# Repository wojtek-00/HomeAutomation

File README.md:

# HomeAutomation

A modular home automation system built around ESPHome, custom PCB design (KiCad), and 3D-printed enclosures.

The project is designed to be **scalable**, allowing multiple independent hardware modules (controller + expanders) that integrate into a single automation system.

---

# 🧠 System Overview

The project is split into two main domains:

## 🧩 hardware/
Contains all physical devices and their design artifacts:

- PCB designs (KiCad)
- 3D enclosures (STEP / CAD files)
- front panels / UI elements
- production-ready snapshots (releases)

Each hardware module is self-contained.

### Current modules:
- `system_controller` – main brain of the system
- `relay_expander` – relay output module (8 outputs + 8 inputs)
- *(future expanders will be added here)*

---

## ⚙️ system/
Contains software and logic:

- ESPHome configurations
- automation logic (e.g. Home Assistant)
- device behavior definitions
- shared system-level configuration

This layer defines **how devices behave**, not how they are built.

---

# 🏗️ Hardware Module Structure

Each hardware module follows the same structure:
 - hardware/<module_name>/
 - current/ # active development (WIP)
 - releases/ # frozen production versions

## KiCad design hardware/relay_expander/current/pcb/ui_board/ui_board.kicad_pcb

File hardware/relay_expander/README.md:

# Sprinkler Expander Module

## Overview

The **Sprinkler Expander Module** is a modular extension board designed for an ESP32-based controller system used with ESPHome home automation projects.

It provides additional digital I/O capabilities as well as flexible power handling for relay-driven actuator systems.

---

## Features

- 8× relay outputs
- 8× digital inputs
- Modular design for sprinkler and automation systems
- Power distribution system with configurable relay supply
- Designed for integration with ESP32 System Controller

---

## Power Architecture

The module contains two independent power domains:

### 1. Logic Power (5V system supply)

- Onboard **bridge rectifier**
- Used to convert optional **AC input into DC**
- Followed by a **5V buck converter**
- Supplies power for:
  - Relay coils
  - ESP32 System Controller (optional power path)

> This allows the system to be powered either from AC or DC sources.

---

### 2. Relay Power Domain

Relay outputs are powered separately from the logic section.

- Default supply: **24VAC (or equivalent external supply)**
- Each relay bank can be powered from a shared rail

#### Individual relay isolation

Each relay channel can be electrically isolated from the main relay power rail by removing a **jumper**.

This allows:
- independent relay supply per channel
- mixed-voltage operation
- custom actuator voltage per output

---

## System Behavior

- Logic section is always powered via 5V rail
- Relay coils may be powered from:
  - shared 24VAC rail (default mode)
  - or independent external supply per channel (jumper removed)

---

## Application

Typical applications:

- Irrigation / sprinkler control systems
- Valve actuation systems
- Distributed relay automation
- Mixed-voltage industrial control logic

---

## Integration

Designed for use with:

- ESP32 System Controller (ESPHome firmware)
- Modular expansion architecture
- DIN rail mounted enclosures

---

## Notes

- Ensure correct jumper configuration before applying relay power
- Do not mix AC and DC relay supply on the same channel
- Verify coil voltage compatibility before deployment

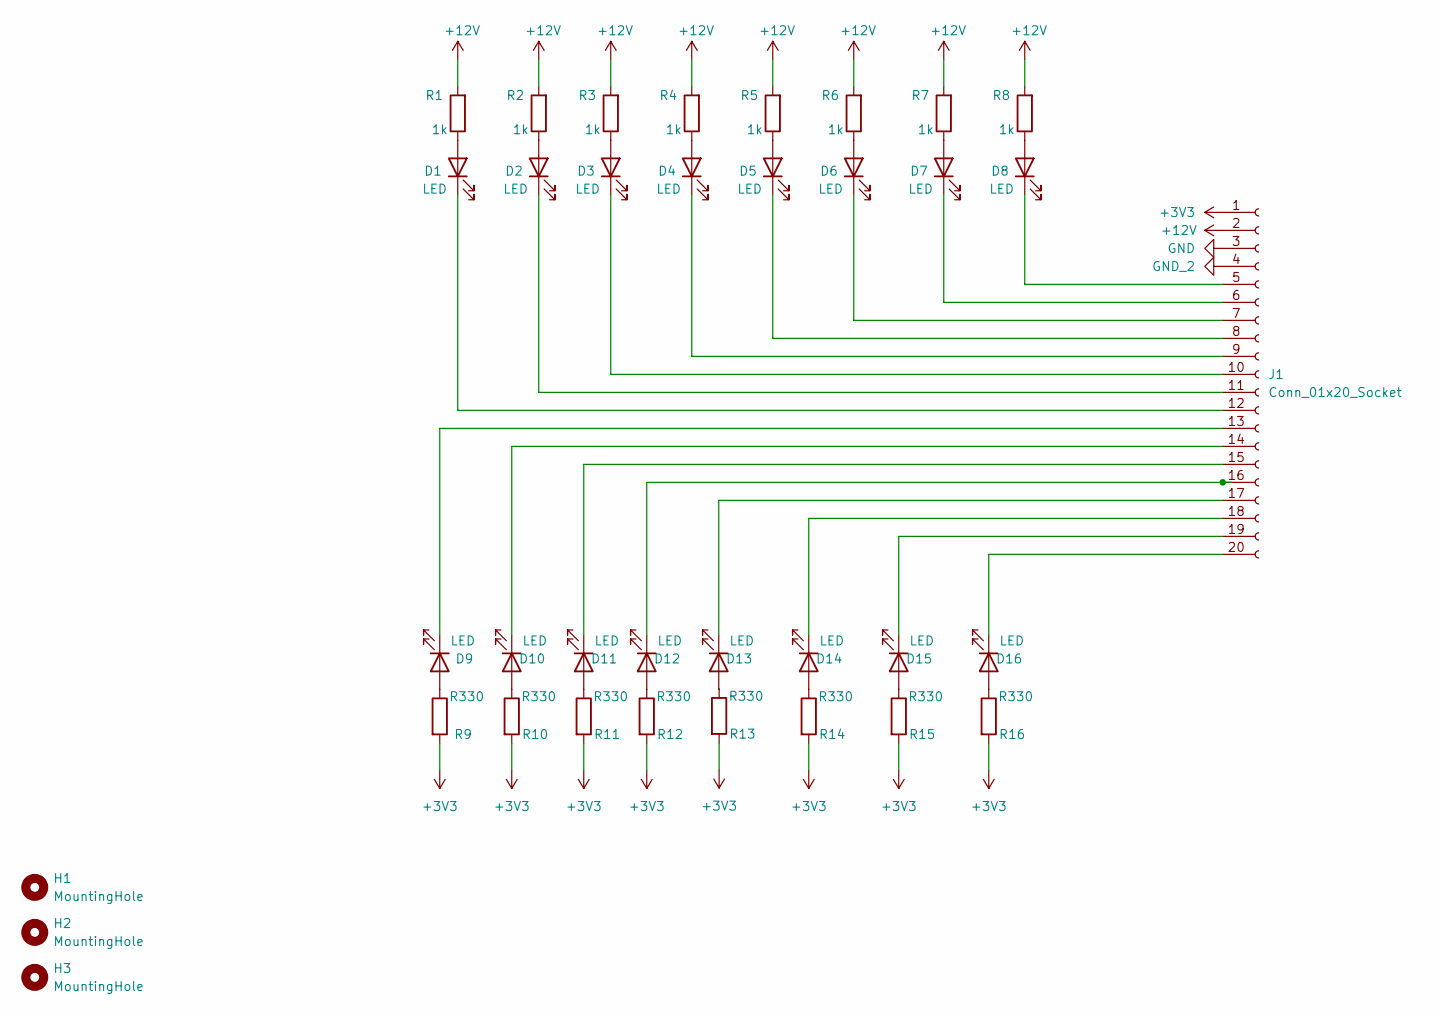
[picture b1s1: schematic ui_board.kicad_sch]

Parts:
D1, D2, D3, D4, D5, D6, D7, D8, D9, D10, D11, D12, D13, D14, D15, D16: LED; LED_1206_3216Metric_Pad1.42x1.75mm_HandSolder
H1, H2, H3: MountingHole; MountingHole_2.2mm_M2_ISO7380_Pad_TopOnly
J1: Conn_01x20_Socket; PinSocket_2x10_P1.27mm_Vertical
R1, R2, R3, R4, R5, R6, R7, R8: 1k; R_1206_3216Metric_Pad1.30x1.75mm_HandSolder
R9, R10, R11, R12, R13, R14, R15, R16: R330; R_1206_3216Metric_Pad1.30x1.75mm_HandSolder

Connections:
+3V3: J1.1, R9.2, R10.2, R11.2, R12.2, R13.2, R14.2, R15.2, R16.2
+12V: J1.2, R1.2, R2.2, R3.2, R4.2, R5.2, R6.2, R7.2, R8.2
GND: J1.3
GND_2: J1.4
unnamed: D1.2 (A), R1.1
unnamed: D1.1 (K), J1.12
unnamed: D2.2 (A), R2.1
unnamed: D2.1 (K), J1.11
unnamed: D3.2 (A), R3.1
unnamed: D3.1 (K), J1.10
unnamed: D4.2 (A), R4.1
unnamed: D4.1 (K), J1.9
unnamed: D5.2 (A), R5.1
unnamed: D5.1 (K), J1.8
unnamed: D6.2 (A), R6.1
unnamed: D6.1 (K), J1.7
unnamed: D7.2 (A), R7.1
unnamed: D7.1 (K), J1.6
unnamed: D8.2 (A), R8.1
unnamed: D8.1 (K), J1.5
unnamed: D9.2 (A), R9.1
unnamed: D9.1 (K), J1.13
unnamed: D10.2 (A), R10.1
unnamed: D10.1 (K), J1.14
unnamed: D11.2 (A), R11.1
unnamed: D11.1 (K), J1.15
unnamed: D12.2 (A), R12.1
unnamed: D12.1 (K), J1.16
unnamed: D13.2 (A), R13.1
unnamed: D13.1 (K), J1.17
unnamed: D14.2 (A), R14.1
unnamed: D14.1 (K), J1.18
unnamed: D15.2 (A), R15.1
unnamed: D15.1 (K), J1.19
unnamed: D16.2 (A), R16.1
unnamed: D16.1 (K), J1.20

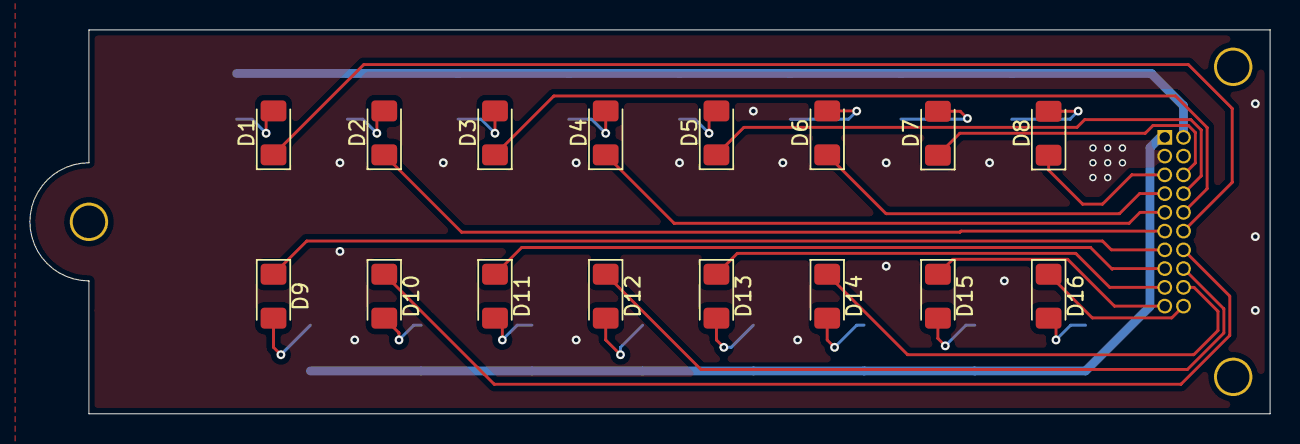
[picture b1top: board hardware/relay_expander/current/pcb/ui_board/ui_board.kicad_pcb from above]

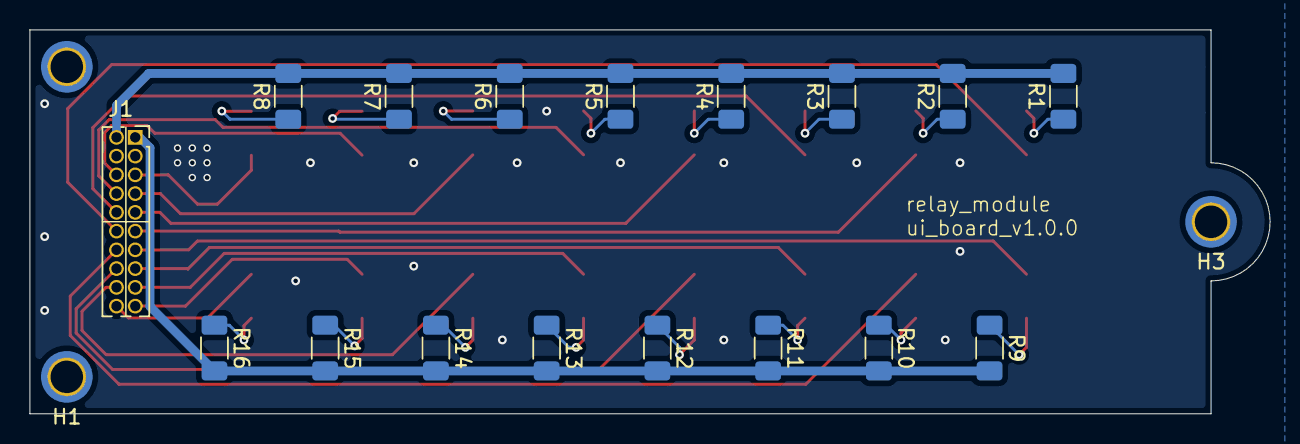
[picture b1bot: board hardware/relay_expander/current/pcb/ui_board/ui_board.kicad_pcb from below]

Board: 2 copper layers, 84.0 x 26.0 mm, 36 parts (20 on the bottom side), 34 nets.

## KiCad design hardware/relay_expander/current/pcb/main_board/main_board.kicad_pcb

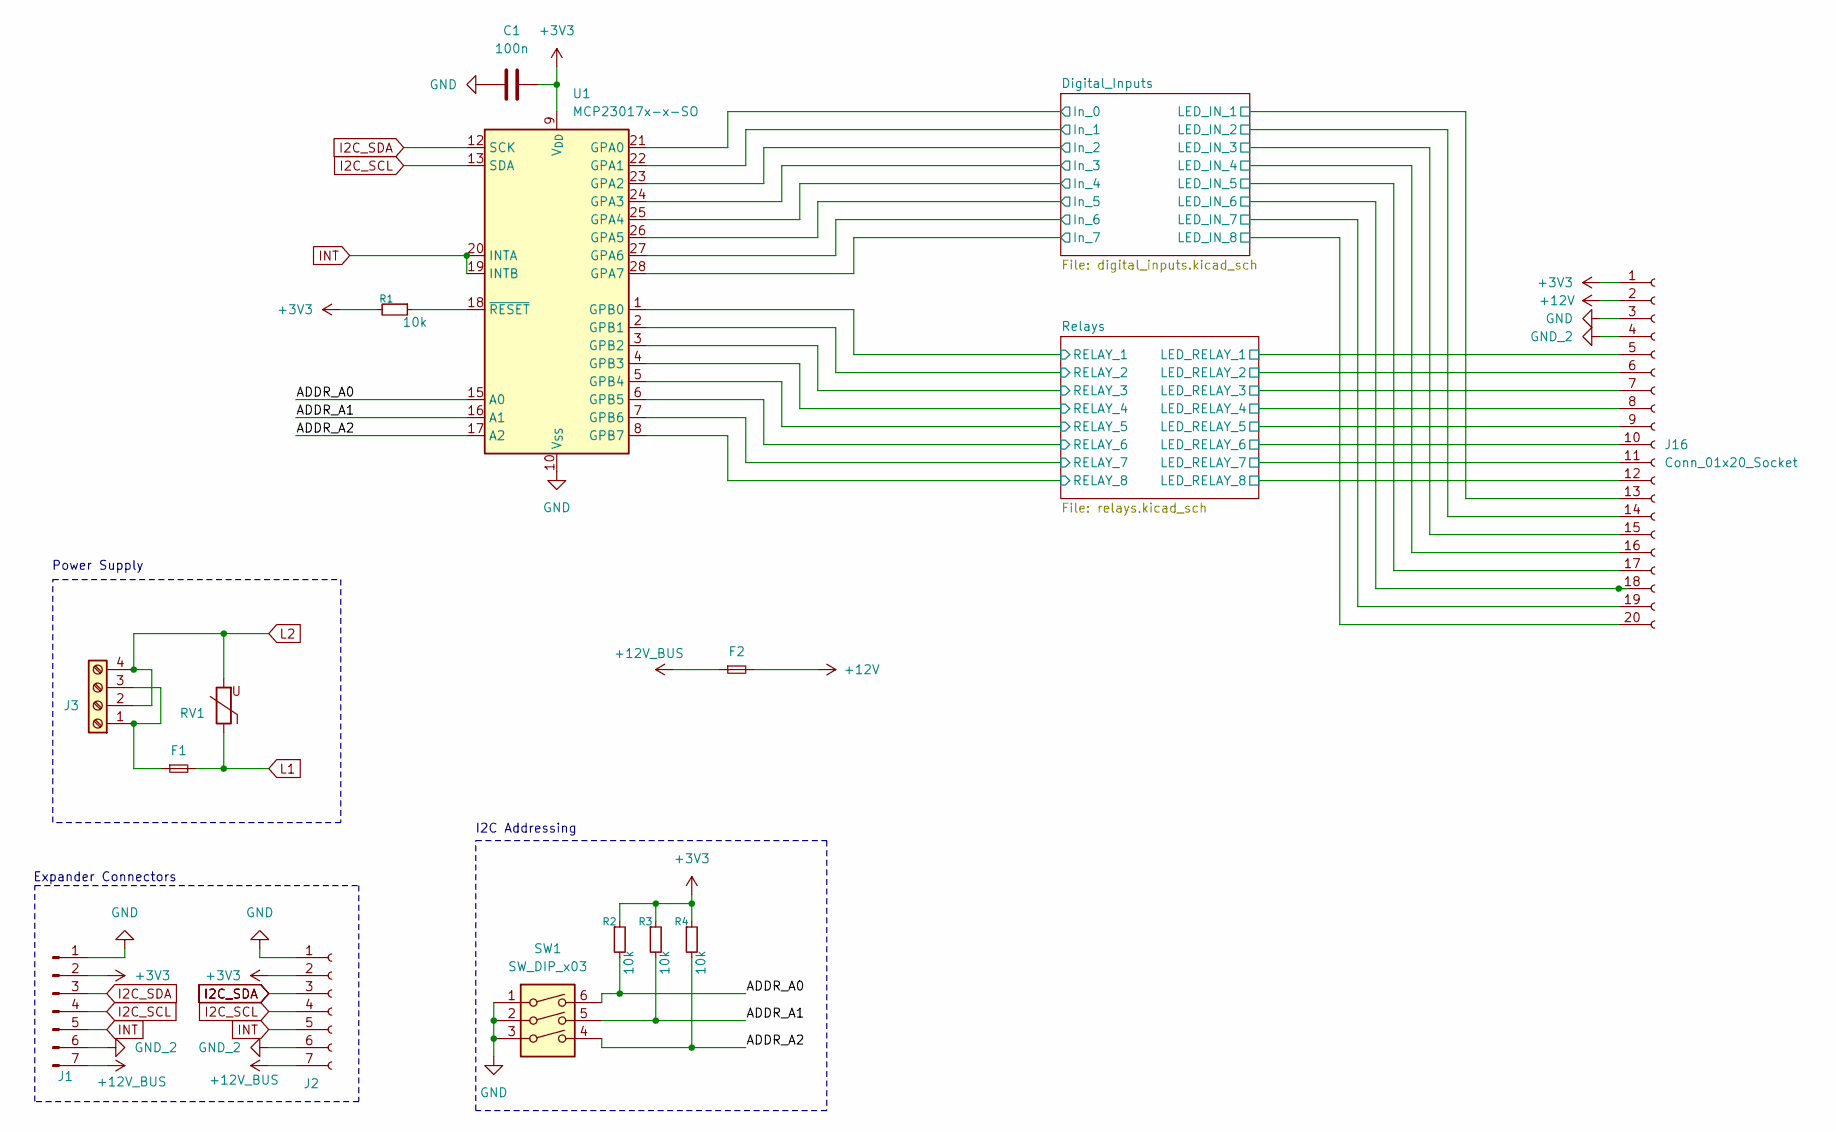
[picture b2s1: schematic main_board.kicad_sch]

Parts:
C1: 100n; C_1206_3216Metric_Pad1.33x1.80mm_HandSolder
F1: 1A, PTC; Fuse_BelFuse_0ZRE0033FF_L11.4mm_W3.8mm
F2: 0.5A; Fuse_1206_3216Metric
J1: Conn_01x07_Socket; PinHeader_1x07_P2.54mm_Horizontal_left
J2: Conn_01x07_Socket; PinSocket_1x07_P2.54mm_Horizontal_Right
J3: Screw_Terminal_01x04; TerminalBlock_Xinya_XY308-2.54-4P_1x04_P2.54mm_Horizontal
J16: Conn_01x20_Socket; PinSocket_2x10_P1.27mm_Vertical
R1, R2, R3, R4: 10k; R_1206_3216Metric_Pad1.30x1.75mm_HandSolder
RV1: 39V, 250A; Fuse_BelFuse_0ZRE0033FF_L11.4mm_W3.8mm
SW1: SW_DIP_x03; SW_DIP_SPSTx03_Slide_6.7x9.18mm_W7.62mm_P2.54mm_LowProfile
U1: MCP23017x-x-SO; SOIC-28W_7.5x17.9mm_P1.27mm

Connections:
+3V3: C1.2, J1.2, J2.2, J16.1, R1.2, R2.1, R3.1, R4.1, U1.9 (V_{DD}); also elsewhere on the board
+12V: F2.2, J16.2; also elsewhere on the board
+12V_BUS: F2.1, J1.7, J2.7
/ADDR_A0: R2.2, SW1.6, U1.15 (A0)
/ADDR_A1: R3.2, SW1.5, U1.16 (A1)
/ADDR_A2: R4.2, SW1.4, U1.17 (A2)
/Digital_Inputs/In_0: J16.13, U1.21 (GPA0); also elsewhere on the board
/Digital_Inputs/In_1: J16.14, U1.22 (GPA1); also elsewhere on the board
/Digital_Inputs/In_2: J16.15, U1.23 (GPA2); also elsewhere on the board
/Digital_Inputs/In_3: J16.16, U1.24 (GPA3); also elsewhere on the board
/Digital_Inputs/In_4: J16.17, U1.25 (GPA4); also elsewhere on the board
/Digital_Inputs/In_5: J16.18, U1.26 (GPA5); also elsewhere on the board
/Digital_Inputs/In_6: J16.19, U1.27 (GPA6); also elsewhere on the board
/Digital_Inputs/In_7: J16.20, U1.28 (GPA7); also elsewhere on the board
/Relays/LED_RELAY_1: J16.5; also elsewhere on the board
/Relays/LED_RELAY_2: J16.6; also elsewhere on the board
/Relays/LED_RELAY_3: J16.7; also elsewhere on the board
/Relays/LED_RELAY_4: J16.8; also elsewhere on the board
/Relays/LED_RELAY_5: J16.9; also elsewhere on the board
/Relays/LED_RELAY_6: J16.10; also elsewhere on the board
/Relays/LED_RELAY_7: J16.11; also elsewhere on the board
/Relays/LED_RELAY_8: J16.12; also elsewhere on the board
/Relays/RELAY_1: U1.1 (GPB0); also elsewhere on the board
/Relays/RELAY_2: U1.2 (GPB1); also elsewhere on the board
/Relays/RELAY_3: U1.3 (GPB2); also elsewhere on the board
/Relays/RELAY_4: U1.4 (GPB3); also elsewhere on the board
/Relays/RELAY_5: U1.5 (GPB4); also elsewhere on the board
/Relays/RELAY_6: U1.6 (GPB5); also elsewhere on the board
/Relays/RELAY_7: U1.7 (GPB6); also elsewhere on the board
/Relays/RELAY_8: U1.8 (GPB7); also elsewhere on the board
GND: C1.1, J1.1, J2.1, J16.3, SW1.1, SW1.2, SW1.3, U1.10 (V_{SS}); also elsewhere on the board
GND_2: J1.6, J2.6, J16.4; also elsewhere on the board
I2C_SCL: J1.4, J2.4, U1.13 (SDA)
I2C_SDA: J1.3, J2.3, U1.12 (SCK)
INT: J1.5, J2.5, U1.19 (INTB), U1.20 (INTA)
L1: F1.2, RV1.1; also elsewhere on the board
L2: J3.2, J3.4, RV1.2; also elsewhere on the board
unnamed: F1.1, J3.1, J3.3
unnamed: R1.1, U1.18 (~RESET)

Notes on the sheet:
Expander Connectors
I2C Addressing
Power Supply

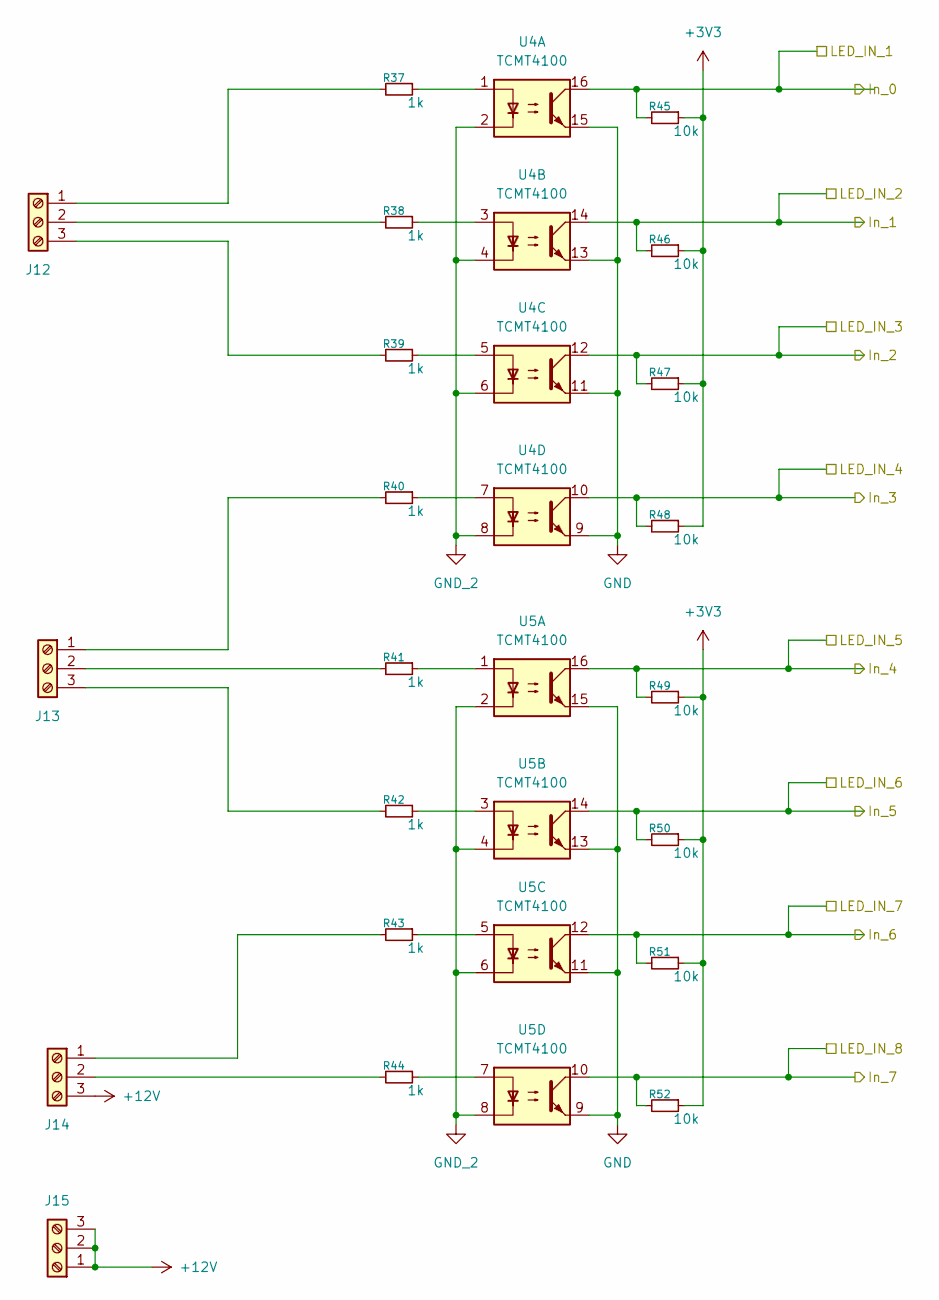
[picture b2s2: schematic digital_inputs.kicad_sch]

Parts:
J12, J13, J14, J15: Screw_Terminal_01x03; TerminalBlock_Phoenix_MPT-0,5-3-2.54_1x03_P2.54mm_Horizontal
R37, R38, R39, R40, R41, R42, R43, R44: 1k; R_1206_3216Metric_Pad1.30x1.75mm_HandSolder
R45, R46, R47, R48, R49, R50, R51, R52: 10k; R_1206_3216Metric_Pad1.30x1.75mm_HandSolder
U4, U5: TCMT4100; SOP-16_4.4x10.4mm_P1.27mm

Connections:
+3V3: R45.1, R46.1, R47.1, R48.1, R49.1, R50.1, R51.1, R52.1; also elsewhere on the board
+12V: J14.3, J15.1, J15.2, J15.3; also elsewhere on the board
/Digital_Inputs/In_0: R45.2, U4.16; also elsewhere on the board
/Digital_Inputs/In_1: R46.2, U4.14; also elsewhere on the board
/Digital_Inputs/In_2: R47.2, U4.12; also elsewhere on the board
/Digital_Inputs/In_3: R48.2, U4.10; also elsewhere on the board
/Digital_Inputs/In_4: R49.2, U5.16; also elsewhere on the board
/Digital_Inputs/In_5: R50.2, U5.14; also elsewhere on the board
/Digital_Inputs/In_6: R51.2, U5.12; also elsewhere on the board
/Digital_Inputs/In_7: R52.2, U5.10; also elsewhere on the board
GND: U4.9, U4.11, U4.13, U4.15, U5.9, U5.11, U5.13, U5.15; also elsewhere on the board
GND_2: U4.2, U4.4, U4.6, U4.8, U5.2, U5.4, U5.6, U5.8; also elsewhere on the board
unnamed: J12.1, R37.2
unnamed: J12.2, R38.2
unnamed: J12.3, R39.2
unnamed: J13.1, R40.2
unnamed: J13.2, R41.2
unnamed: J13.3, R42.2
unnamed: J14.1, R43.2
unnamed: J14.2, R44.2
unnamed: R37.1, U4.1
unnamed: R38.1, U4.3
unnamed: R39.1, U4.5
unnamed: R40.1, U4.7
unnamed: R41.1, U5.1
unnamed: R42.1, U5.3
unnamed: R43.1, U5.5
unnamed: R44.1, U5.7

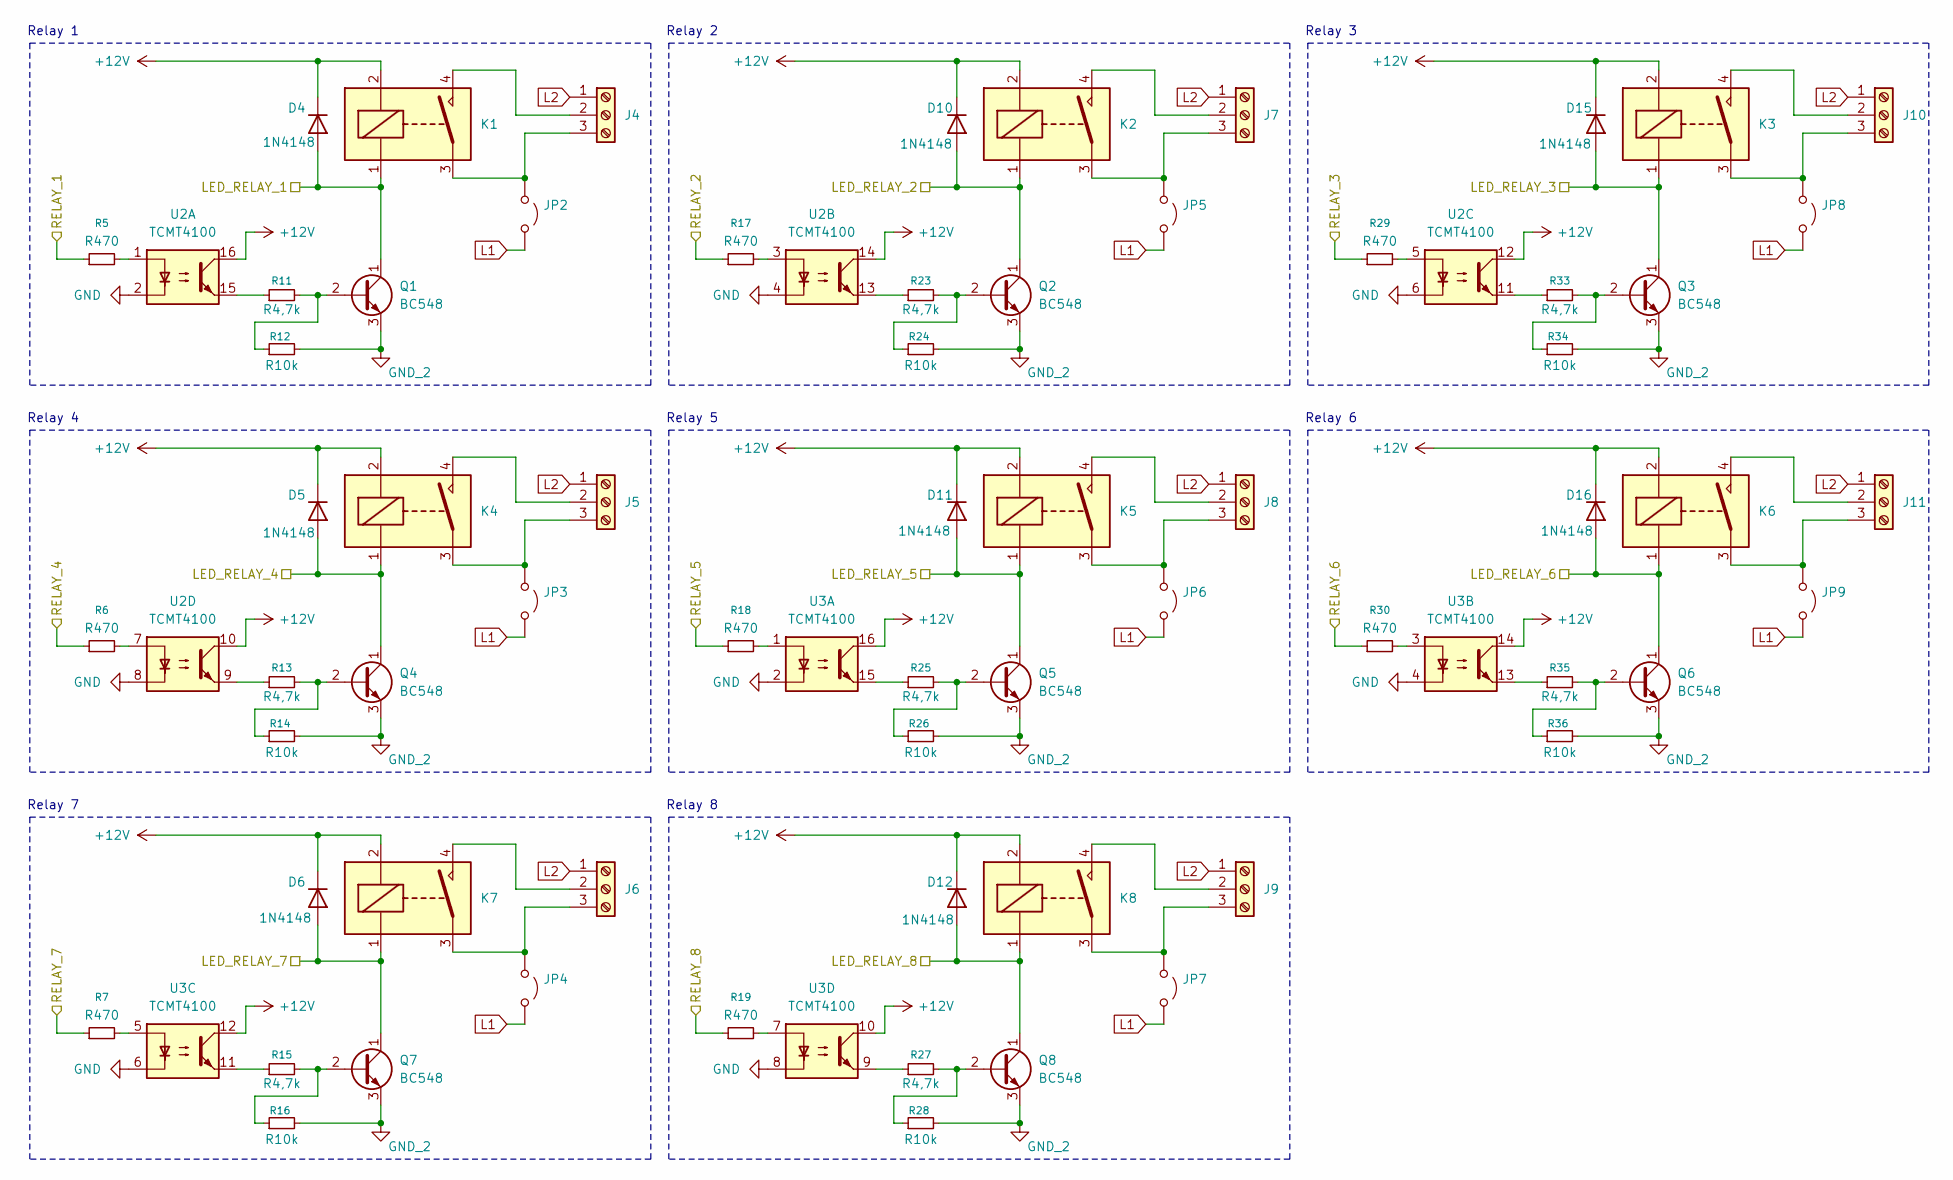
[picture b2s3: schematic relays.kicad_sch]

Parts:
D4, D5, D6, D10, D11, D12, D15, D16: 1N4148; D_SOD-123
J4, J5, J6, J7, J8, J9, J10, J11: Screw_Terminal_01x03; TerminalBlock_Phoenix_MPT-0,5-3-2.54_1x03_P2.54mm_Horizonta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
JP2, JP3, JP4, JP5, JP6, JP7, JP8, JP9: Jumper_2_Open; PinHeader_1x02_P2.54mm_Vertical
K1, K2, K3, K4, K5, K6, K7, K8: HF46F-12-HS1; relay_HF46F
Q1, Q2, Q3, Q4, Q5, Q6, Q7, Q8: BC548; TO-92_Inline
R5, R6, R7, R17, R18, R19, R29, R30: R470; R_1206_3216Metric_Pad1.30x1.75mm_HandSolder
R11, R13, R15, R23, R25, R27, R33, R35: R4,7k; R_1206_3216Metric_Pad1.30x1.75mm_HandSolder
R12, R14, R16, R24, R26, R28, R34, R36: R10k; R_1206_3216Metric_Pad1.30x1.75mm_HandSolder
U2, U3: TCMT4100; SOP-16_4.4x10.4mm_P1.27mm

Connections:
+12V: D4.1 (K), D5.1 (K), D6.1 (K), D10.1 (K), D11.1 (K), D12.1 (K), D15.1 (K), D16.1 (K), K1.2, K2.2, K3.2, K4.2, K5.2, K6.2, K7.2, K8.2, U2.10, U2.12, U2.14, U2.16, U3.10, U3.12, U3.14, U3.16; also elsewhere on the board
/Relays/LED_RELAY_1: D4.2 (A), K1.1, Q1.1 (C); also elsewhere on the board
/Relays/LED_RELAY_2: D10.2 (A), K2.1, Q2.1 (C); also elsewhere on the board
/Relays/LED_RELAY_3: D15.2 (A), K3.1, Q3.1 (C); also elsewhere on the board
/Relays/LED_RELAY_4: D5.2 (A), K4.1, Q4.1 (C); also elsewhere on the board
/Relays/LED_RELAY_5: D11.2 (A), K5.1, Q5.1 (C); also elsewhere on the board
/Relays/LED_RELAY_6: D16.2 (A), K6.1, Q6.1 (C); also elsewhere on the board
/Relays/LED_RELAY_7: D6.2 (A), K7.1, Q7.1 (C); also elsewhere on the board
/Relays/LED_RELAY_8: D12.2 (A), K8.1, Q8.1 (C); also elsewhere on the board
/Relays/RELAY_1: R5.1; also elsewhere on the board
/Relays/RELAY_2: R17.1; also elsewhere on the board
/Relays/RELAY_3: R29.1; also elsewhere on the board
/Relays/RELAY_4: R6.1; also elsewhere on the board
/Relays/RELAY_5: R18.1; also elsewhere on the board
/Relays/RELAY_6: R30.1; also elsewhere on the board
/Relays/RELAY_7: R7.1; also elsewhere on the board
/Relays/RELAY_8: R19.1; also elsewhere on the board
GND: U2.2, U2.4, U2.6, U2.8, U3.2, U3.4, U3.6, U3.8; also elsewhere on the board
GND_2: Q1.3 (E), Q2.3 (E), Q3.3 (E), Q4.3 (E), Q5.3 (E), Q6.3 (E), Q7.3 (E), Q8.3 (E), R12.2, R14.2, R16.2, R24.2, R26.2, R28.2, R34.2, R36.2; also elsewhere on the board
L1: JP2.2 (B), JP3.2 (B), JP4.2 (B), JP5.2 (B), JP6.2 (B), JP7.2 (B), JP8.2 (B), JP9.2 (B); also elsewhere on the board
L2: J4.1, J5.1, J6.1, J7.1, J8.1, J9.1, J10.1, J11.1; also elsewhere on the board
unnamed: J4.2, K1.4
unnamed: J4.3, JP2.1 (A), K1.3
unnamed: J5.2, K4.4
unnamed: J5.3, JP3.1 (A), K4.3
unnamed: J6.2, K7.4
unnamed: J6.3, JP4.1 (A), K7.3
unnamed: J7.2, K2.4
unnamed: J7.3, JP5.1 (A), K2.3
unnamed: J8.2, K5.4
unnamed: J8.3, JP6.1 (A), K5.3
unnamed: J9.2, K8.4
unnamed: J9.3, JP7.1 (A), K8.3
unnamed: J10.2, K3.4
unnamed: J10.3, JP8.1 (A), K3.3
unnamed: J11.2, K6.4
unnamed: J11.3, JP9.1 (A), K6.3
unnamed: Q1.2 (B), R11.2, R12.1
unnamed: Q2.2 (B), R23.2, R24.1
unnamed: Q3.2 (B), R33.2, R34.1
unnamed: Q4.2 (B), R13.2, R14.1
unnamed: Q5.2 (B), R25.2, R26.1
unnamed: Q6.2 (B), R35.2, R36.1
unnamed: Q7.2 (B), R15.2, R16.1
unnamed: Q8.2 (B), R27.2, R28.1
unnamed: R5.2, U2.1
unnamed: R6.2, U2.7
unnamed: R7.2, U3.5
unnamed: R11.1, U2.15
unnamed: R13.1, U2.9
unnamed: R15.1, U3.11
unnamed: R17.2, U2.3
unnamed: R18.2, U3.1
unnamed: R19.2, U3.7
unnamed: R23.1, U2.13
unnamed: R25.1, U3.15
unnamed: R27.1, U3.9
unnamed: R29.2, U2.5
unnamed: R30.2, U3.3
unnamed: R33.1, U2.11
unnamed: R35.1, U3.13

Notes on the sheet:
Relay 3
Relay 8
Relay 2
Relay 7
Relay 6
Relay 5
Relay 4
Relay 1

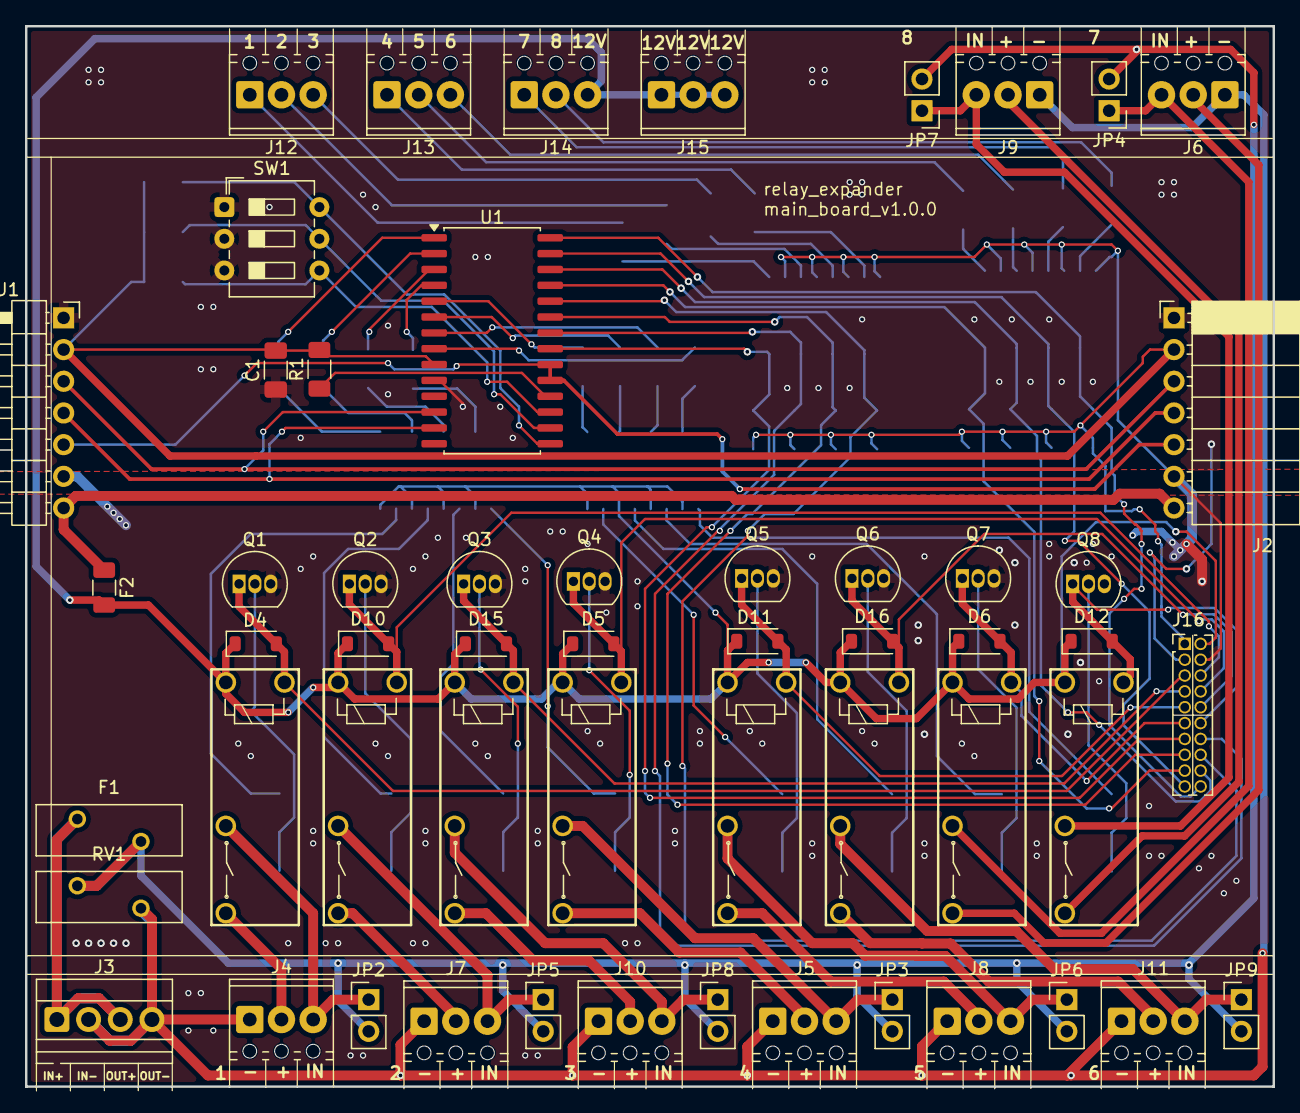
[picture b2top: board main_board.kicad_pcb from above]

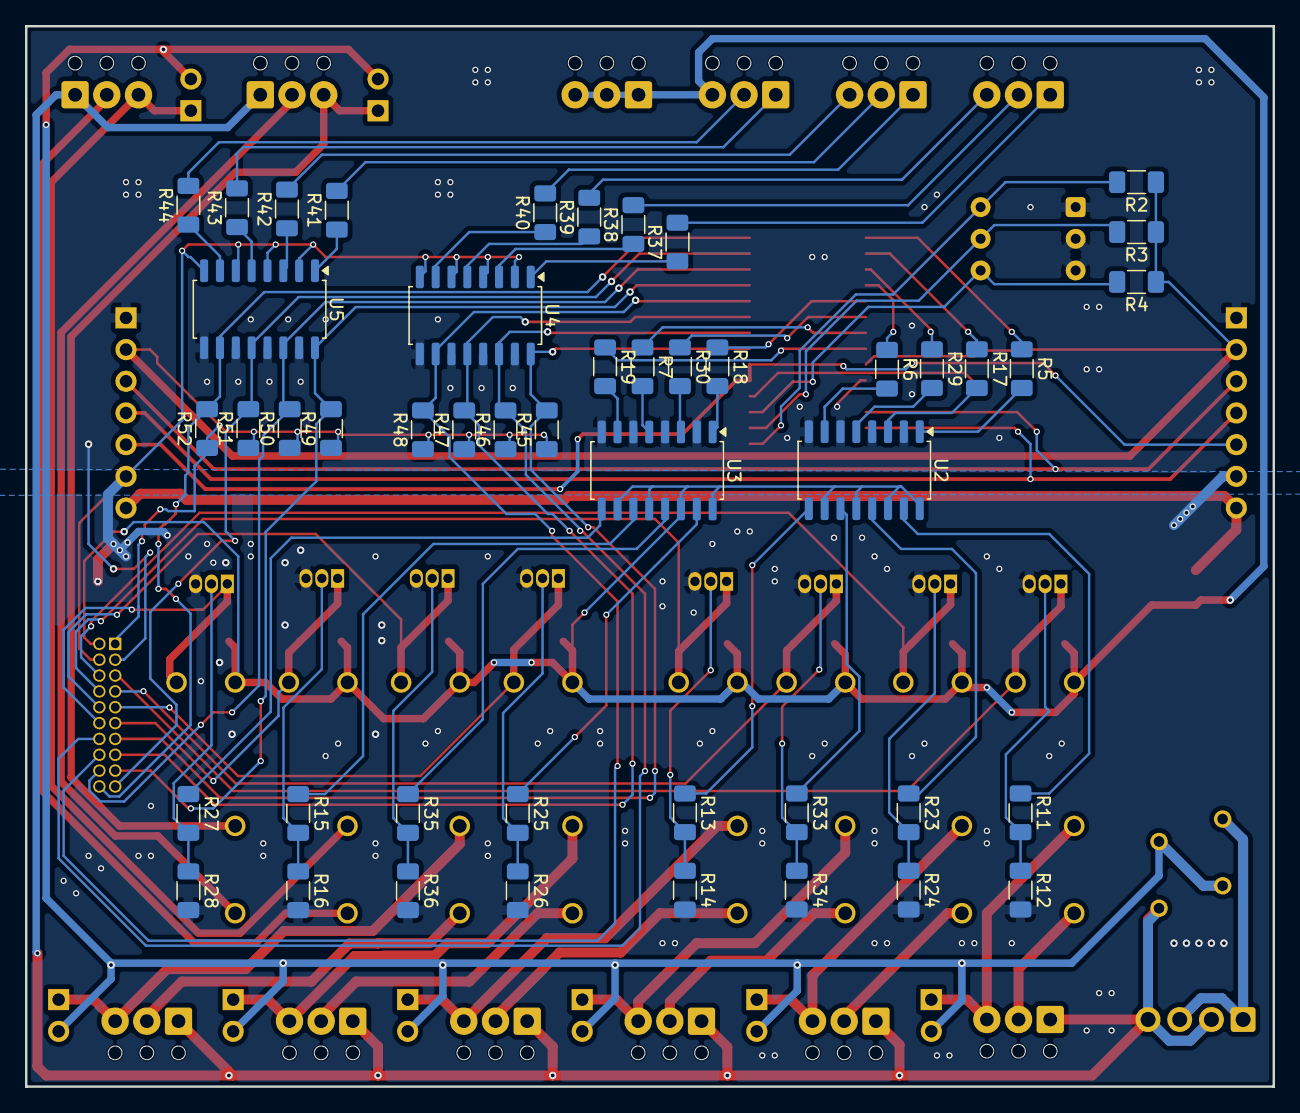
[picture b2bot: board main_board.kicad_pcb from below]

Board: 2 copper layers, 100.0 x 85.0 mm, 102 parts (47 on the bottom side), 95 nets.

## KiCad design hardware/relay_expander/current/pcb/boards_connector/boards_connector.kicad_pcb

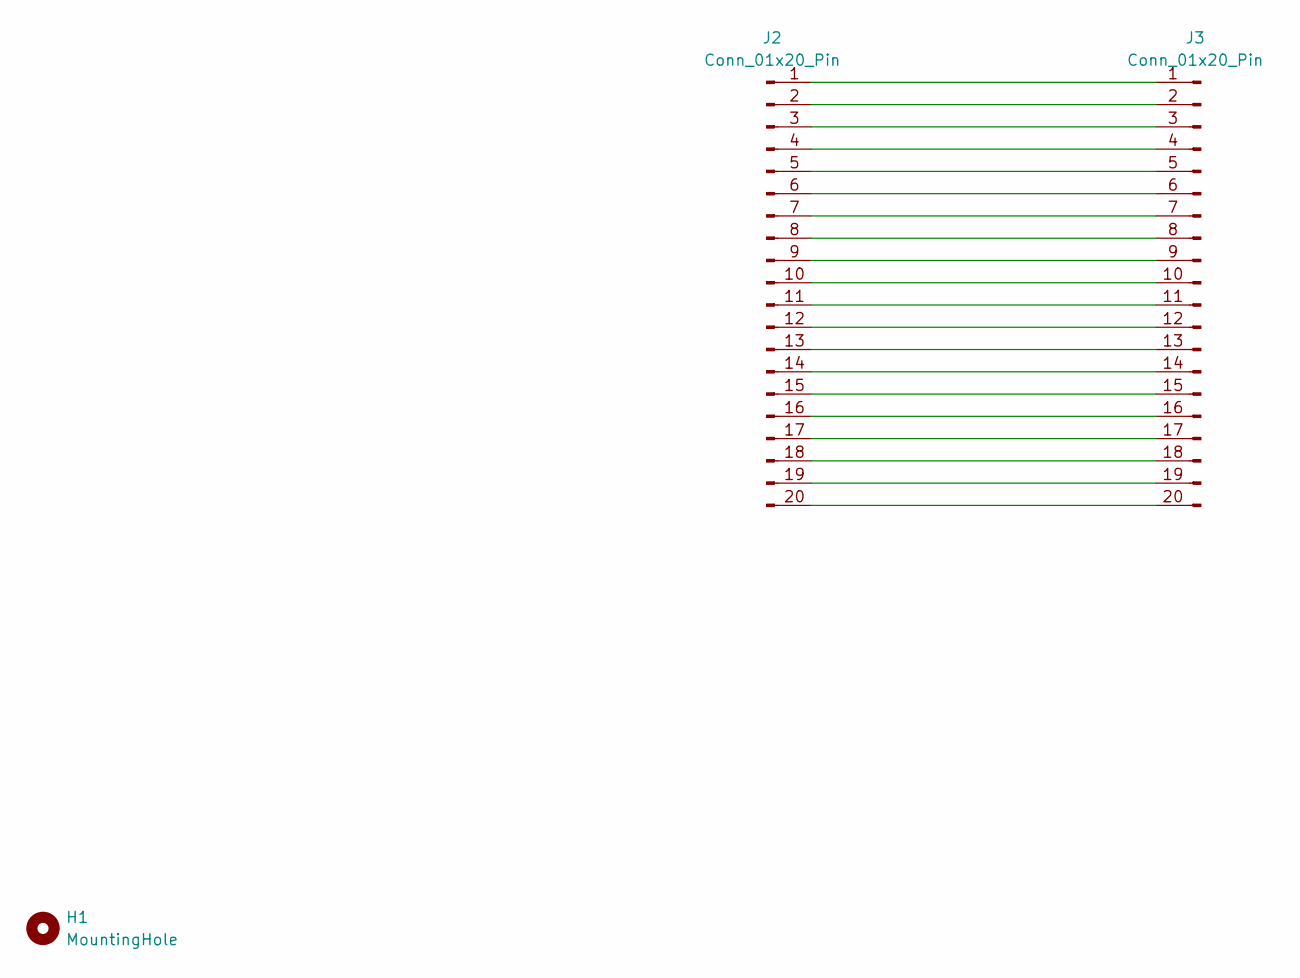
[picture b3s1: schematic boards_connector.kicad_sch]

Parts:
H1: MountingHole; MountingHole_2.2mm_M2_ISO7380_Pad_TopOnly
J2, J3: Conn_01x20_Pin; PinHeader_2x10_P1.27mm_Horizontal

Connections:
unnamed: J2.1, J3.1
unnamed: J2.2, J3.2
unnamed: J2.3, J3.3
unnamed: J2.4, J3.4
unnamed: J2.5, J3.5
unnamed: J2.6, J3.6
unnamed: J2.7, J3.7
unnamed: J2.8, J3.8
unnamed: J2.9, J3.9
unnamed: J2.10, J3.10
unnamed: J2.11, J3.11
unnamed: J2.12, J3.12
unnamed: J2.13, J3.13
unnamed: J2.14, J3.14
unnamed: J2.15, J3.15
unnamed: J2.16, J3.16
unnamed: J2.17, J3.17
unnamed: J2.18, J3.18
unnamed: J2.19, J3.19
unnamed: J2.20, J3.20

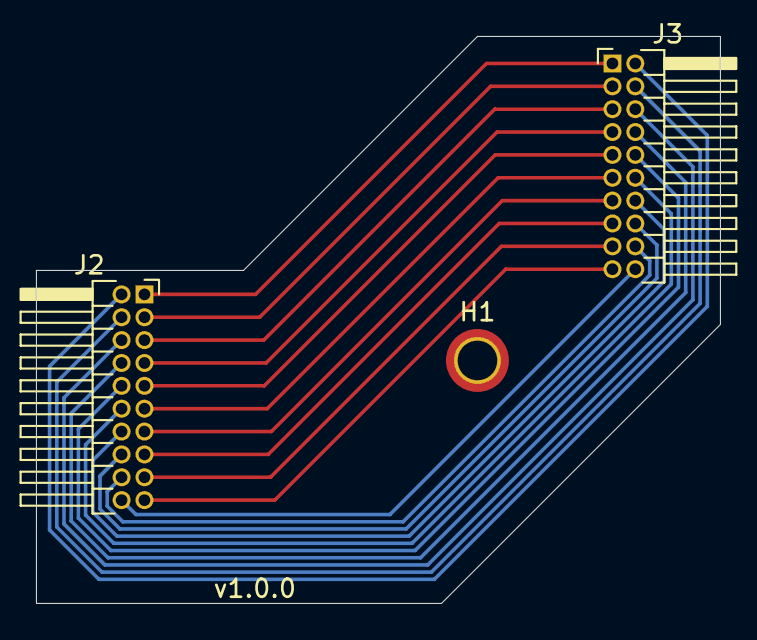
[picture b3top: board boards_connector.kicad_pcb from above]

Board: 2 copper layers, 38.0 x 31.5 mm, 3 parts (0 on the bottom side), 20 nets.
